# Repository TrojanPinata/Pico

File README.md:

# Pico
This project is a precursor to a future project which I aim to use a RP2040 as the microcontroller as the core of a keyboard, very similar to my original keyboard but with PCBA.

The goal of this was to prove the feasability of using PCBA as well as prove my ability to make a functioning RP2040 microcontroller board. The Pi Pico was simply chosen as it was a very accessible option.

If you want to use this project, it should be noted that this is open source, but I would rather you simply use this as a reference. Putting that much confidence in someone elses work is dangerous, and I cannot guarantee spec with the original.

The only major changes with these boards vs the real deal are the addition of a reset button and usb-c header (something that should be on the original :| )

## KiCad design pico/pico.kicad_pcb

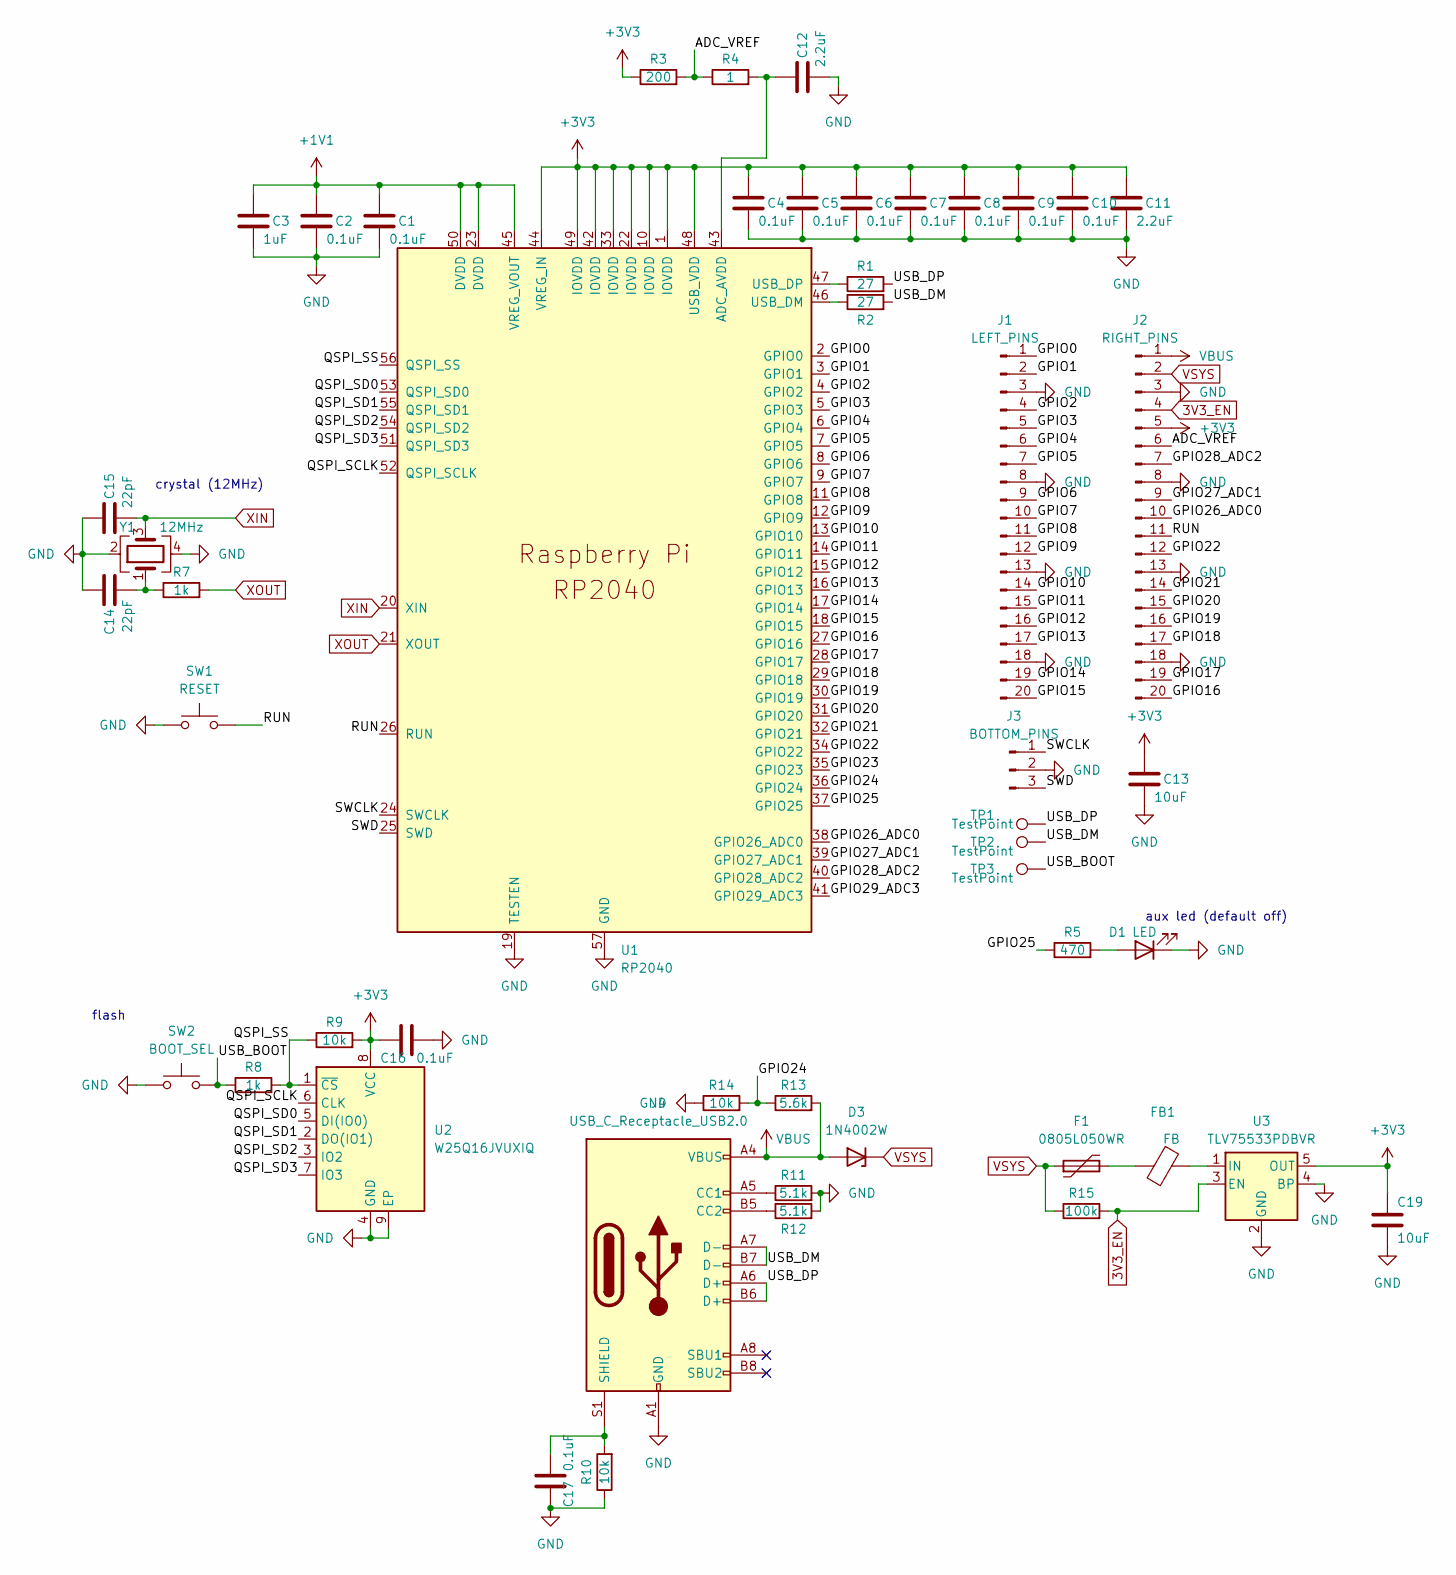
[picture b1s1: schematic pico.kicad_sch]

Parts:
C1, C2, C4, C5, C6, C7, C8, C9, C10, C16, C17: 0.1uF; C_0402_1005Metric
C3: 1uF; C_0402_1005Metric
C11, C12: 2.2uF; C_0402_1005Metric
C13, C19: 10uF; C_0402_1005Metric
C14, C15: 22pF; C_0402_1005Metric
D1: LED; LED_0402_1005Metric
D3: 1N4002W; D_SOD-123
F1: 0805L050WR; Fuse_0805_2012Metric
FB1: FB; R_0402_1005Metric
J1: LEFT_PINS; PinHeader_1x20_P2.54mm_Vertical
J2: RIGHT_PINS; PinHeader_1x20_P2.54mm_Vertical
J3: BOTTOM_PINS; PinHeader_1x03_P2.54mm_Vertical
J4: USB_C_Receptacle_USB2.0; HRO-TYPE-C-31-M-12
R1, R2: 27; R_0402_1005Metric
R3: 200; R_0402_1005Metric
R4: 1; R_0402_1005Metric
R5: 470; R_0402_1005Metric
R7, R8: 1k; R_0402_1005Metric
R9, R10, R14: 10k; R_0402_1005Metric
R11, R12: 5.1k; R_0402_1005Metric
R13: 5.6k; R_0402_1005Metric
R15: 100k; R_0402_1005Metric
SW1: RESET; SW_Push_SPST_NO_Alps_SKRK
SW2: BOOT_SEL; SW_Push_SPST_NO_Alps_SKRK
TP1, TP2, TP3: TestPoint; CustomTestPoint
U1: RP2040; RP2040-QFN-56
U2: W25Q16JVUXIQ; SON-8-1EP_3x2mm_P0.5mm_EP1.4x1.6mm
U3: TLV75533PDBVR; SOT-23-5
Y1: 12MHz; Crystal_SMD_3225-4Pin_3.2x2.5mm

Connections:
3V3_EN: J2.4, R15.2, U3.3 (EN)
+1V1: C1.1, C2.1, C3.1, U1.23 (DVDD), U1.45 (VREG_VOUT), U1.50 (DVDD)
+3V3: C4.1, C5.1, C6.1, C7.1, C8.1, C9.1, C10.1, C11.1, C13.1, C16.2, C19.1, J2.5, R3.1, R9.2, U1.1 (IOVDD), U1.10 (IOVDD), U1.22 (IOVDD), U1.33 (IOVDD), U1.42 (IOVDD), U1.44 (VREG_IN), U1.48 (USB_VDD), U1.49 (IOVDD), U2.8 (VCC), U3.5 (OUT)
/ADC_VREF: J2.6, R3.2, R4.1
/GPIO0: J1.1, U1.2 (GPIO0)
/GPIO1: J1.2, U1.3 (GPIO1)
/GPIO2: J1.4, U1.4 (GPIO2)
/GPIO3: J1.5, U1.5 (GPIO3)
/GPIO4: J1.6, U1.6 (GPIO4)
/GPIO5: J1.7, U1.7 (GPIO5)
/GPIO6: J1.9, U1.8 (GPIO6)
/GPIO7: J1.10, U1.9 (GPIO7)
/GPIO8: J1.11, U1.11 (GPIO8)
/GPIO9: J1.12, U1.12 (GPIO9)
/GPIO10: J1.14, U1.13 (GPIO10)
/GPIO11: J1.15, U1.14 (GPIO11)
/GPIO12: J1.16, U1.15 (GPIO12)
/GPIO13: J1.17, U1.16 (GPIO13)
/GPIO14: J1.19, U1.17 (GPIO14)
/GPIO15: J1.20, U1.18 (GPIO15)
/GPIO16: J2.20, U1.27 (GPIO16)
/GPIO17: J2.19, U1.28 (GPIO17)
/GPIO18: J2.17, U1.29 (GPIO18)
/GPIO19: J2.16, U1.30 (GPIO19)
/GPIO20: J2.15, U1.31 (GPIO20)
/GPIO21: J2.14, U1.32 (GPIO21)
/GPIO22: J2.12, U1.34 (GPIO22)
/GPIO23: U1.35 (GPIO23)
/GPIO24: R13.1, R14.2, U1.36 (GPIO24)
/GPIO25: R5.1, U1.37 (GPIO25)
/GPIO26_ADC0: J2.10, U1.38 (GPIO26_ADC0)
/GPIO27_ADC1: J2.9, U1.39 (GPIO27_ADC1)
/GPIO28_ADC2: J2.7, U1.40 (GPIO28_ADC2)
/GPIO29_ADC3: U1.41 (GPIO29_ADC3)
/QSPI_SCLK: U1.52 (QSPI_SCLK), U2.6 (CLK)
/QSPI_SD0: U1.53 (QSPI_SD0), U2.5 (DI(IO0))
/QSPI_SD1: U1.55 (QSPI_SD1), U2.2 (DO(IO1))
/QSPI_SD2: U1.54 (QSPI_SD2), U2.3 (IO2)
/QSPI_SD3: U1.51 (QSPI_SD3), U2.7 (IO3)
/QSPI_SS: R8.2, R9.1, U1.56 (QSPI_SS), U2.1 (~CS)
/RUN: J2.11, SW1.2, U1.26 (RUN)
/SWCLK: J3.1, U1.24 (SWCLK)
/SWD: J3.3, U1.25 (SWD)
/USB_BOOT: R8.1, SW2.2, TP3.1
/USB_DM: J4.A7 (D-), J4.B7 (D-), R2.2, TP2.1
/USB_DP: J4.A6 (D+), J4.B6 (D+), R1.2, TP1.1
GND: C1.2, C2.2, C3.2, C4.2, C5.2, C6.2, C7.2, C8.2, C9.2, C10.2, C11.2, C12.2, C13.2, C14.2, C15.1, C16.1, C17.2, C19.2, D1.1 (K), J1.3, J1.8, J1.13, J1.18, J2.3, J2.8, J2.13, J2.18, J3.2, J4.A1 (GND), J4.A12 (GND), J4.B1 (GND), J4.B12 (GND), R10.1, R11.2, R12.2, R14.1, SW1.1, SW2.1, U1.19 (TESTEN), U1.57 (GND), U2.4 (GND), U2.9 (EP), U3.2 (GND), U3.4 (BP), Y1.2, Y1.4
unnamed: C14.1, R7.1, Y1.1
unnamed: D1.2 (A), R5.2
unnamed: F1.2, FB1.2
unnamed: J4.A5 (CC1), R11.1
unnamed: J4.B5 (CC2), R12.1
unnamed: C17.1, J4.S1 (SHIELD), R10.2
unnamed: C12.1, R4.2, U1.43 (ADC_AVDD)
unnamed: R2.1, U1.46 (USB_DM)
unnamed: R1.1, U1.47 (USB_DP)
unnamed: FB1.1, U3.1 (IN)
VBUS: D3.2 (A), J2.1, J4.A4 (VBUS), J4.A9 (VBUS), J4.B4 (VBUS), J4.B9 (VBUS), R13.2
VSYS: D3.1 (K), F1.1, J2.2, R15.1
XIN: C15.2, U1.20 (XIN), Y1.3
XOUT: R7.2, U1.21 (XOUT)

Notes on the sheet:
aux led (default off)
crystal (12MHz)
flash

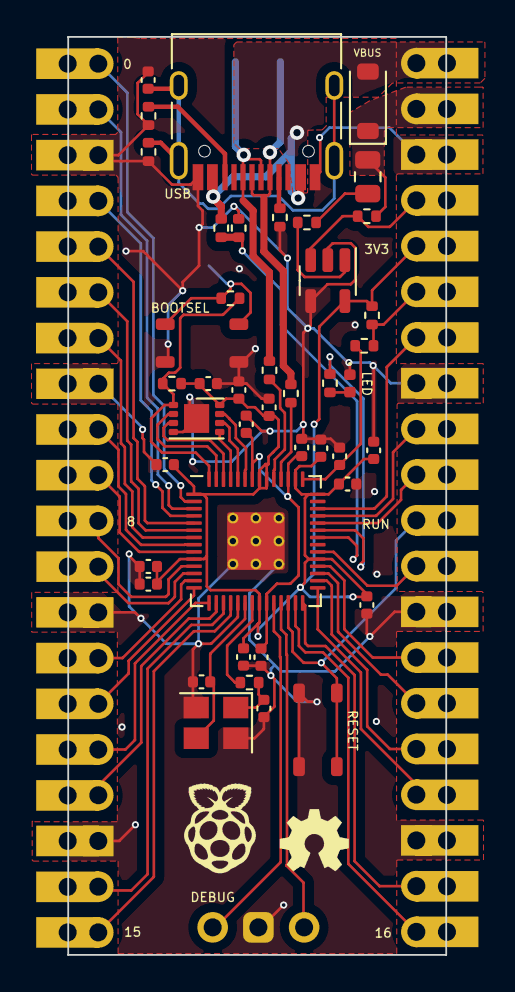
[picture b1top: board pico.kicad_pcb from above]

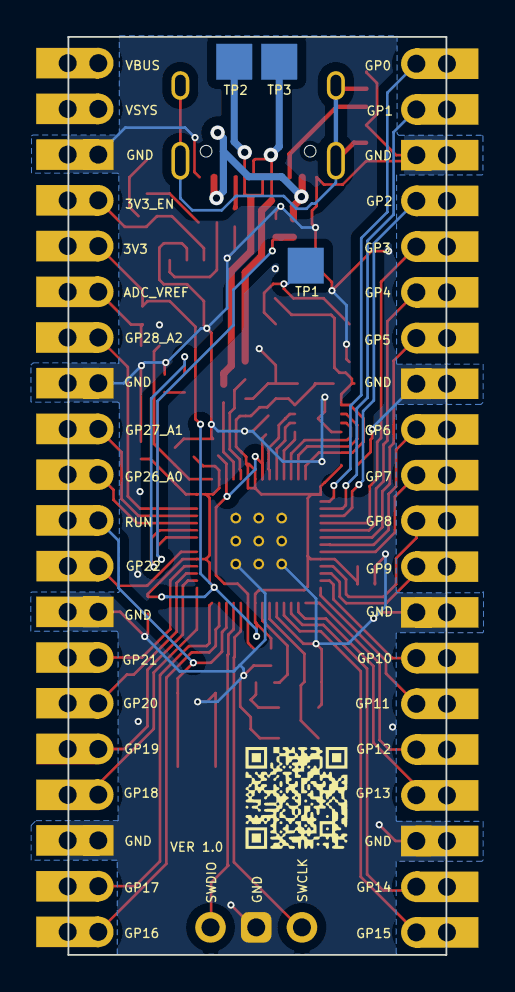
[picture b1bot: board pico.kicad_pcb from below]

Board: 2 copper layers, 21.0 x 51.0 mm, 49 parts (3 on the bottom side), 59 nets.

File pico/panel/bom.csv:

Designator,Footprint,Quantity,Value,LCSC Part #
"C1_6, C1_5, C1_4, C1_3, C1_2, C1, C10_6, C10_5, C10_4, C10_3, C10_2, C10, C16_6, C16_5, C16_4, C16_3, C16_2, C16, C17_6, C17_5, C17_4, C17_3, C17_2, C17, C2_6, C2_5, C2_4, C2_3, C2_2, C2, C4_6, C4_5, C4_4, C4_3, C4_2, C4, C5_6, C5_5, C5_4, C5_3, C5_2, C5, C6_6, C6_5, C6_4, C6_3, C6_2, C6, C7_6, C7_5, C7_4, C7_3, C7_2, C7, C8_6, C8_5, C8_4, C8_3, C8_2, C8, C9_6, C9_5, C9_4, C9_3, C9_2, C9",0402,66,0.1uF,C1525
"C11_6, C11_5, C11_4, C11_3, C11_2, C11, C12_6, C12_5, C12_4, C12_3, C12_2, C12",0402,12,2.2uF,C107369
"C13_6, C13_5, C13_4, C13_3, C13_2, C13, C19_6, C19_5, C19_4, C19_3, C19_2, C19",0402,12,10uF,C15525
"C14_6, C14_5, C14_4, C14_3, C14_2, C14, C15_6, C15_5, C15_4, C15_3, C15_2, C15",0402,12,22pF,C1554
"C3_6, C3_5, C3_4, C3_3, C3_2, C3",0402,6,1uF,C14445
"D1_6, D1_5, D1_4, D1_3, D1_2, D1",0402,6,LED,C2856703
"D3_6, D3_5, D3_4, D3_3, D3_2, D3",D_SOD-123,6,1N4002W,C169542
"F1_6, F1_5, F1_4, F1_3, F1_2, F1",0805,6,0805L050WR,C207022
"FB1_6, FB1_5, FB1_4, FB1_3, FB1_2, FB1",0402,6,FB,C160973
"J4_6, J4_5, J4_4, J4_3, J4_2, J4",HRO-TYPE-C-31-M-12,6,USB_C_Receptacle_USB2.0,C165948
"R1_6, R1_5, R1_4, R1_3, R1_2, R1, R2_6, R2_5, R2_4, R2_3, R2_2, R2",0402,12,27,C25100
"R10_6, R10_5, R10_4, R10_3, R10_2, R10, R14_6, R14_5, R14_4, R14_3, R14_2, R14, R9_6, R9_5, R9_4, R9_3, R9_2, R9",0402,18,10k,C25744
"R11_6, R11_5, R11_4, R11_3, R11_2, R11, R12_6, R12_5, R12_4, R12_3, R12_2, R12",0402,12,5.1k,C25905
"R13_6, R13_5, R13_4, R13_3, R13_2, R13",0402,6,5.6k,C25908
"R15_6, R15_5, R15_4, R15_3, R15_2, R15",0402,6,100k,C60491
"R3_6, R3_5, R3_4, R3_3, R3_2, R3",0402,6,200,C25092
"R4_6, R4_5, R4_4, R4_3, R4_2, R4",0402,6,1,C25086
"R5_6, R5_5, R5_4, R5_3, R5_2, R5",0402,6,470,C25900
"R7_6, R7_5, R7_4, R7_3, R7_2, R7, R8_6, R8_5, R8_4, R8_3, R8_2, R8",0402,12,1k,C11702
"SW1_6, SW1_5, SW1_4, SW1_3, SW1_2, SW1",SW_Push_SPST_NO_Alps_SKRK,6,RESET,C139797
"SW2_6, SW2_5, SW2_4, SW2_3, SW2_2, SW2",SW_Push_SPST_NO_Alps_SKRK,6,BOOT_SEL,C139797
"U1_6, U1_5, U1_4, U1_3, U1_2, U1",RP2040-QFN-56,6,RP2040,C2040
"U2_6, U2_5, U2_4, U2_3, U2_2, U2",SON-8-1EP_3x2mm_P0.5mm_EP1.4x1.6mm,6,W25Q16JVUXIQ,C2843335
"U3_6, U3_5, U3_4, U3_3, U3_2, U3",SOT-23-5,6,TLV75533PDBVR,C404027
"Y1_6, Y1_5, Y1_4, Y1_3, Y1_2, Y1",Crystal_SMD_3225-4Pin_3.2x2.5mm,6,12MHz,C9002

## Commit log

2024-05-10 v1.0 w/ panels
2024-05-14 bom modifications
2024-05-17 add license
    I have to add licenses to all of my repos bc people are stealing some of them and selling them (╥﹏╥)
